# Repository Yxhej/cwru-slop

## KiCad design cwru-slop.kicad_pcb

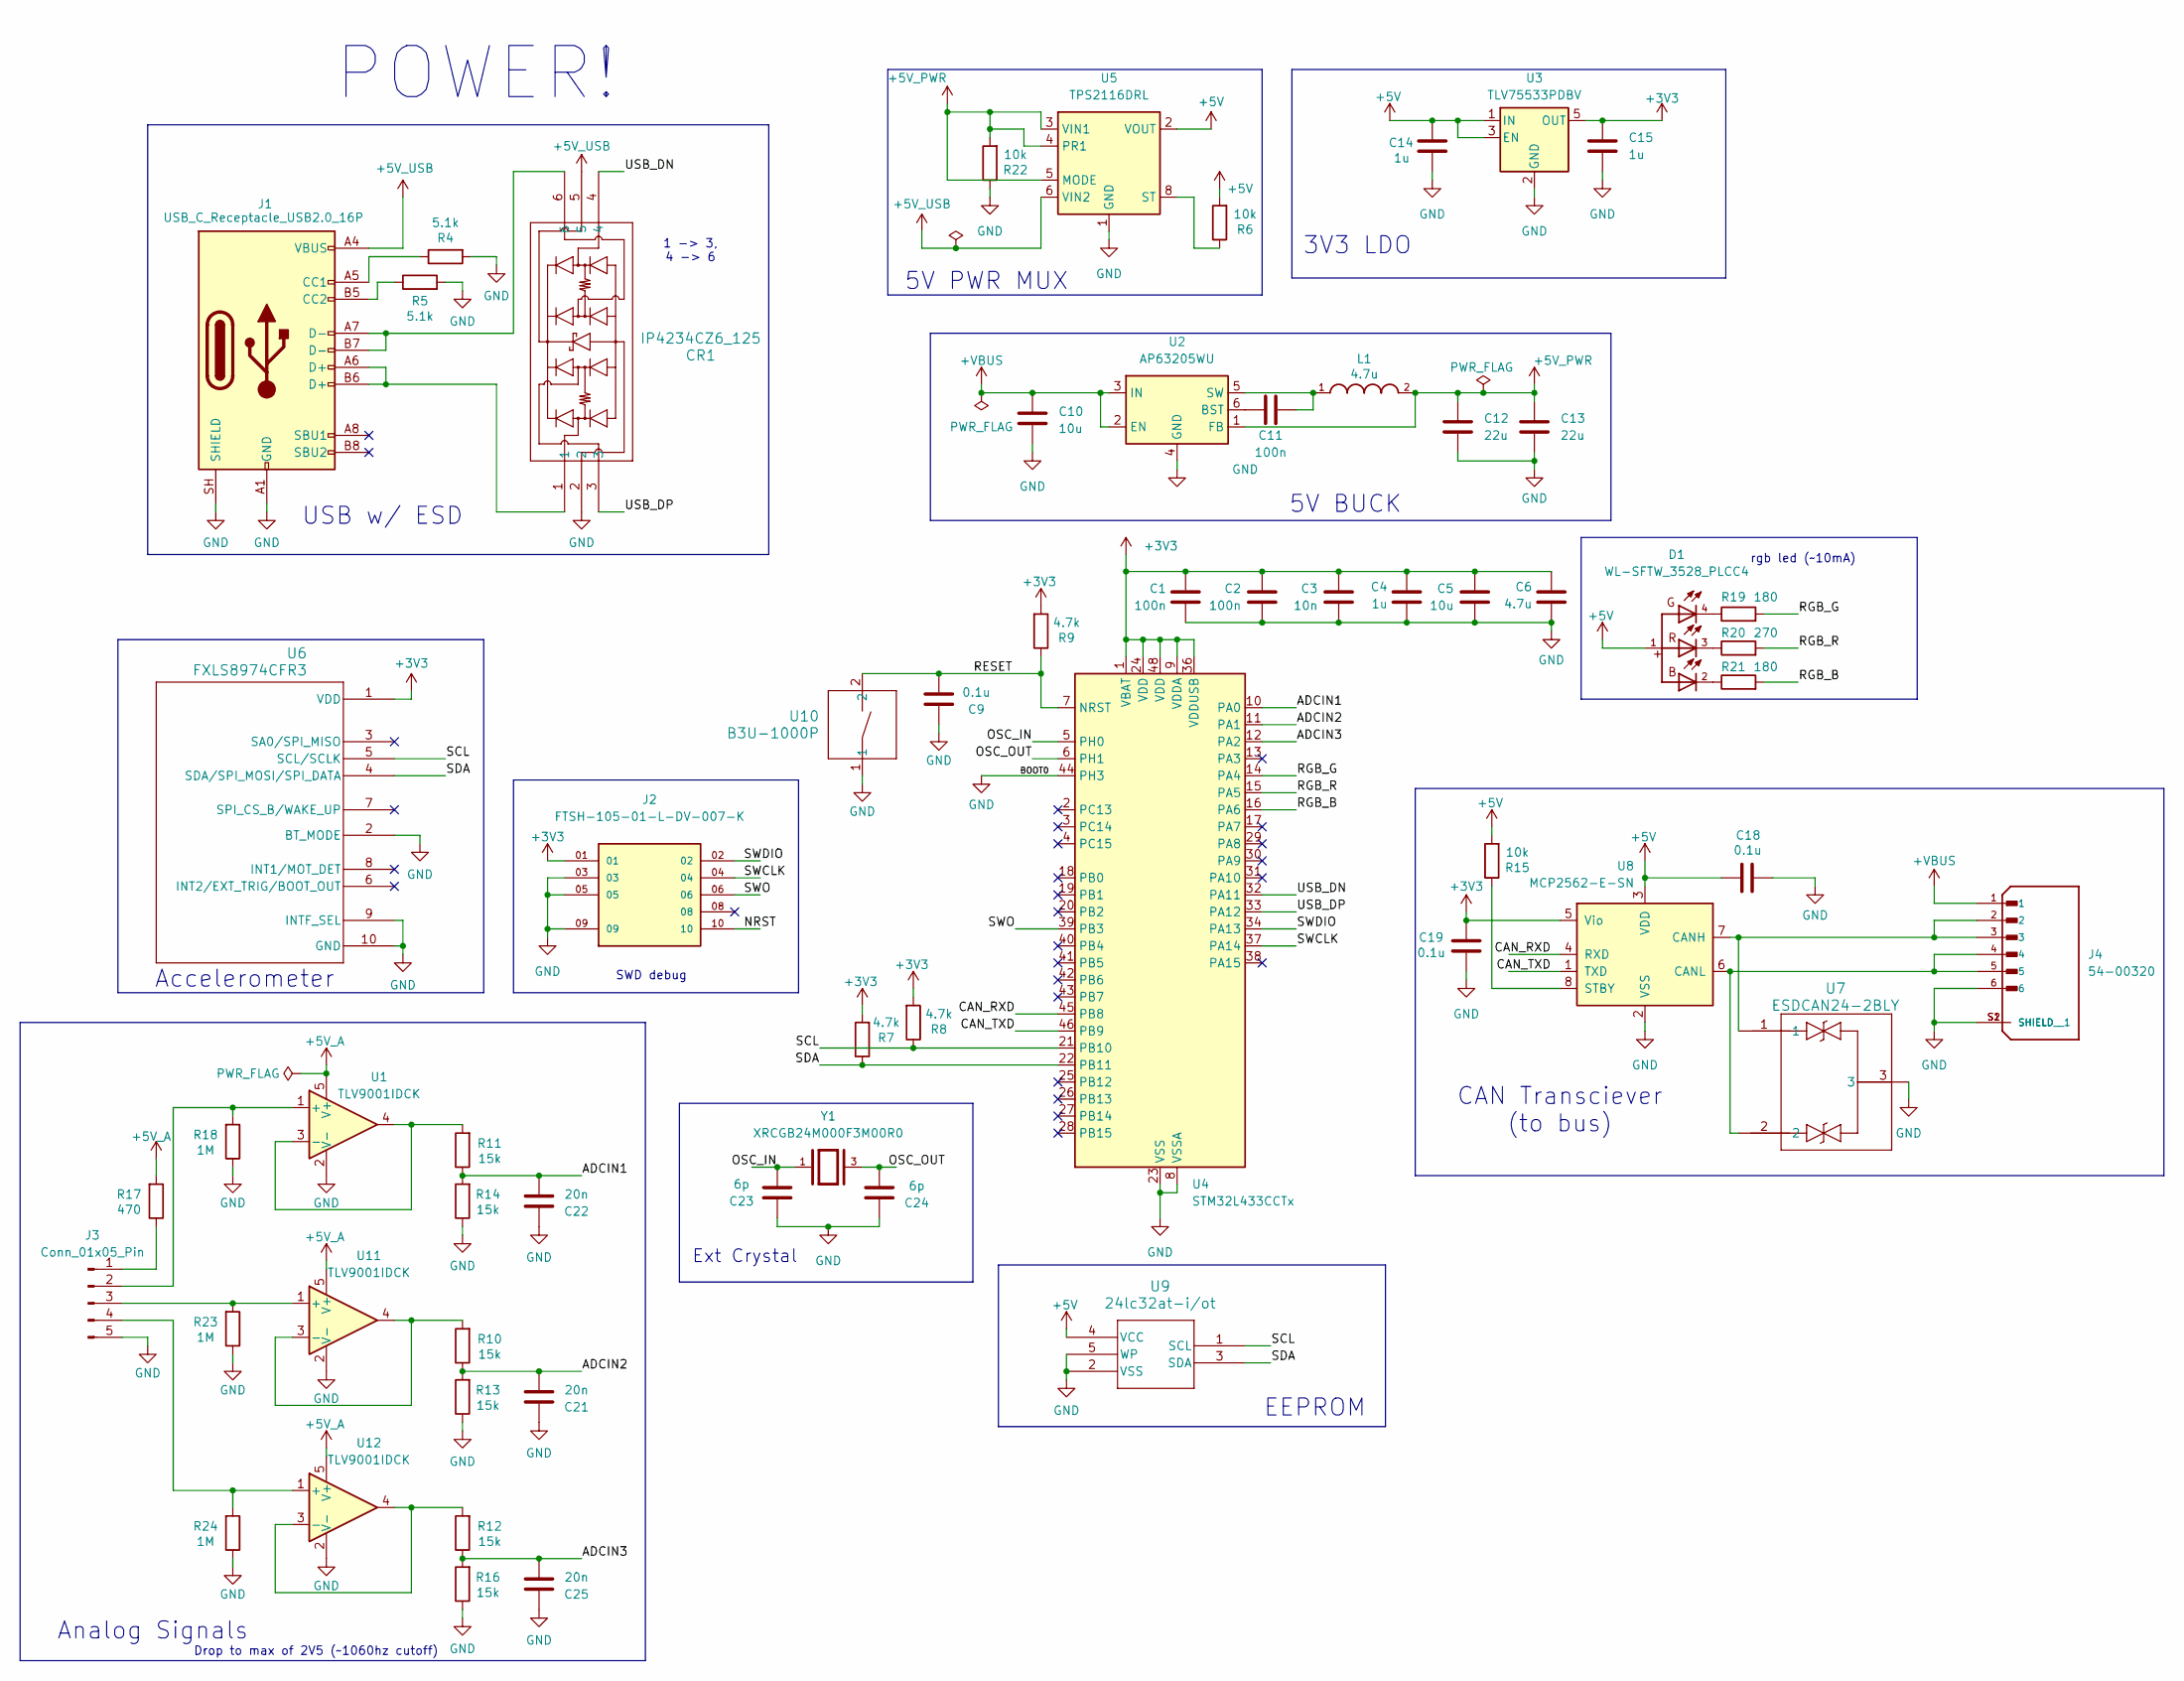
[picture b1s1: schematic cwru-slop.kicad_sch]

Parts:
C1, C2, C11: 100n; C_0603_1608Metric_Pad1.08x0.95mm_HandSolder
C3: 10n; C_0603_1608Metric_Pad1.08x0.95mm_HandSolder
C4, C14, C15: 1u; C_0603_1608Metric_Pad1.08x0.95mm_HandSolder
C5, C10: 10u; C_0603_1608Metric_Pad1.08x0.95mm_HandSolder
C6: 4.7u; C_0603_1608Metric_Pad1.08x0.95mm_HandSolder
C9, C18, C19: 0.1u; C_0603_1608Metric_Pad1.08x0.95mm_HandSolder
C12, C13: 22u; C_0603_1608Metric_Pad1.08x0.95mm_HandSolder
C21, C22, C25: 20n; C_0603_1608Metric_Pad1.08x0.95mm_HandSolder
C23, C24: 6p; C_0603_1608Metric_Pad1.08x0.95mm_HandSolder
CR1: IP4234CZ6_125; TSOP6_SOT457_NEX
D1: WL-SFTW_3528_PLCC4
J1: USB_C_Receptacle_USB2.0_16P; USB_C_Receptacle_GCT_USB4105-xx-A_16P_TopMnt_Horizontal
J2: FTSH-105-01-L-DV-007-K; SAMTEC_FTSH-105-01-L-DV-007-K; PARTREV H
J3: Conn_01x05_Pin; DIP-20_W7.62mm
J4: 54-00320; TENSILITY_54-00320; PARTREV A
L1: 4.7u; INDC2520X120N
R4, R5: 5.1k; R_0603_1608Metric_Pad0.98x0.95mm_HandSolder
R6, R15, R22: 10k; R_0603_1608Metric_Pad0.98x0.95mm_HandSolder
R7, R8, R9: 4.7k; R_0603_1608Metric_Pad0.98x0.95mm_HandSolder
R10, R11, R12, R13, R14, R16: 15k; R_0603_1608Metric_Pad0.98x0.95mm_HandSolder
R17: 470; R_0603_1608Metric_Pad0.98x0.95mm_HandSolder
R18, R23, R24: 1M; R_0603_1608Metric_Pad0.98x0.95mm_HandSolder
R19, R21: 180; R_0603_1608Metric_Pad0.98x0.95mm_HandSolder
R20: 270; R_0603_1608Metric_Pad0.98x0.95mm_HandSolder
U1, U11, U12: TLV9001IDCK; SOT-353_SC-70-5
U2: AP63205WU; TSOT-23-6
U3: TLV75533PDBV; SOT-23-5
U4: STM32L433CCTx; LQFP-48_7x7mm_P0.5mm
U5: TPS2116DRL; SOT-583-8
U6: FXLS8974CFR3; DFN10_2X2_STM
U7: ESDCAN24-2BLY; SOT_24-2BLY_STM
U8: MCP2562-E-SN; SOIC-8_3.9x4.9mm_P1.27mm
U9: 24lc32at-i/ot; SOT-24-5_MC_MCH
U10: B3U-1000P
Y1: XRCGB24M000F3M00R0; OSC_XRCGB24M000F3M00R0; PARTREV N/A

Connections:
+3V3: C1.1, C2.1, C3.1, C4.1, C5.1, C6.1, C15.1, C19.2, J2.01, R7.2, R8.2, R9.2, U3.5 (OUT), U4.1 (VBAT), U4.9 (VDDA), U4.24 (VDD), U4.36 (VDDUSB), U4.48 (VDD), U6.1 (VDD), U8.5 (Vio)
+5V: C14.1, C18.1, D1.1, R6.2, R15.2, U3.1 (IN), U3.3 (EN), U5.2 (VOUT), U5.7 (VOUT), U8.3 (VDD), U9.4 (VCC)
+5V_A: R17.2, U1.5 (V+), U11.5 (V+), U12.5 (V+)
+5V_PWR: C12.1, C13.2, L1.2, R22.2, U2.1 (FB), U5.3 (VIN1), U5.4 (PR1), U5.5 (MODE)
+5V_USB: CR1.5, J1.A4 (VBUS), J1.A9 (VBUS), J1.B4 (VBUS), J1.B9 (VBUS), U5.6 (VIN2)
+VBUS: C10.1, J4.1, U2.2 (EN), U2.3 (IN)
/ADCIN1: C22.2, R11.1, R14.2, U4.10 (PA0)
/ADCIN2: C21.2, R10.1, R13.2, U4.11 (PA1)
/ADCIN3: C25.2, R12.1, R16.2, U4.12 (PA2)
/CAN_RXD: U4.45 (PB8), U8.4 (RXD)
/CAN_TXD: U4.46 (PB9), U8.1 (TXD)
/NRST: J2.10
/OSC_IN: C23.2, U4.5 (PH0), Y1.1
/OSC_OUT: C24.2, U4.6 (PH1), Y1.3
/RESET: C9.2, R9.1, U4.7 (NRST), U10.2
/RGB_B: R21.2, U4.16 (PA6)
/RGB_G: R19.2, U4.14 (PA4)
/RGB_R: R20.2, U4.15 (PA5)
/SCL: R8.1, U4.21 (PB10), U6.5 (SCL/SCLK), U9.1 (SCL)
/SDA: R7.1, U4.22 (PB11), U6.4 (SDA/SPI_MOSI/SPI_DATA), U9.3 (SDA)
/SWCLK: J2.04, U4.37 (PA14)
/SWDIO: J2.02, U4.34 (PA13)
/SWO: J2.06, U4.39 (PB3)
/USB_DN: CR1.4, U4.32 (PA11)
/USB_DP: CR1.3, U4.33 (PA12)
GND: C1.2, C2.2, C3.2, C4.2, C5.2, C6.2, C9.1, C10.2, C12.2, C13.1, C14.2, C15.2, C18.2, C19.1, C21.1, C22.1, C23.1, C24.1, C25.1, CR1.2, J1.A1 (GND), J1.A12 (GND), J1.B1 (GND), J1.B12 (GND), J1.SH (SHIELD), J2.03, J2.05, J2.09, J3.5, J4.6, J4.S1 (SHIELD), J4.S2 (SHIELD__1), R4.2, R5.2, R13.1, R14.1, R16.1, R18.1, R22.1, R23.1, R24.1, U1.2 (V-), U2.4 (GND), U3.2 (GND), U4.8 (VSSA), U4.23 (VSS), U4.35 (VSS), U4.44 (PH3), U4.47 (VSS), U5.1 (GND), U6.2 (BT_MODE), U6.9 (INTF_SEL), U6.10 (GND), U7.3, U8.2 (VSS), U9.2 (VSS), U9.5 (WP), U10.1, U11.2 (V-), U12.2 (V-)
unnamed: CR1.1, J1.A6 (D+), J1.B6 (D+)
unnamed: CR1.6, J1.A7 (D-), J1.B7 (D-)
unnamed: D1.2, R21.1
unnamed: D1.3, R20.1
unnamed: D1.4, R19.1
unnamed: J1.A5 (CC1), R4.1
unnamed: J1.B5 (CC2), R5.1
unnamed: J3.1, R17.1
unnamed: J3.2, R18.2, U1.1 (+)
unnamed: J3.3, R23.2, U11.1 (+)
unnamed: J3.4, R24.2, U12.1 (+)
unnamed: R11.2, U1.3 (-), U1.4
unnamed: C11.1, U2.6 (BST)
unnamed: C11.2, L1.1, U2.5 (SW)
unnamed: R6.1, U5.8 (ST)
unnamed: J4.2, J4.3, U7.1, U8.7 (CANH)
unnamed: J4.4, J4.5, U7.2, U8.6 (CANL)
unnamed: R15.1, U8.8 (STBY)
unnamed: R10.2, U11.3 (-), U11.4
unnamed: R12.2, U12.3 (-), U12.4

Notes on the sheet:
Ext Crystal
3V3 LDO
CAN Transciever (to bus)
5V BUCK
Drop to max of 2V5 (~1060hz cutoff)
Analog Signals
rgb led (~10mA)
5V PWR MUX
POWER!
USB w/ ESD
SWD debug
1 -> 3, 4 -> 6
EEPROM
Accelerometer

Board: 2 copper layers, 61 parts (0 on the bottom side), 45 nets, no tracks yet.

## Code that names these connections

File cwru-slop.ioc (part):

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Mcu.Name=STM32L433C(B-C)Tx
Mcu.Package=LQFP48
Mcu.UserName=STM32L433CCTx
PA0.Signal=ADCx_IN5
PA1.Signal=ADCx_IN6
PA11.Mode=Device
PA11.Signal=USB_DM
PA12.Mode=Device
PA12.Signal=USB_DP
PA13\ (JTMS-SWDIO).Signal=SYS_JTMS-SWDIO
PA14\ (JTCK-SWCLK).Signal=SYS_JTCK-SWCLK
PA2.Signal=ADCx_IN7
PA4.Signal=GPIO_Output
PA5.Signal=GPIO_Output
PA6.Signal=GPIO_Output
PB10.Mode=I2C
PB10.Signal=I2C2_SCL
PB11.Mode=I2C
PB11.Signal=I2C2_SDA
PB3\ (JTDO-TRACESWO).Signal=SYS_JTDO-SWO
PB8.Mode=CAN_Activate
PB8.Signal=CAN1_RX
PB9.Mode=CAN_Activate
PB9.Signal=CAN1_TX
PH0-OSC_IN\ (PH0).Mode=HSE-External-Oscillator
PH0-OSC_IN\ (PH0).Signal=RCC_OSC_IN
PH1-OSC_OUT\ (PH1).Mode=HSE-External-Oscillator
PH1-OSC_OUT\ (PH1).Signal=RCC_OSC_OUT
RCC.HSE_VALUE=8000000
RCC.SYSCLKFreq_VALUE=80000000
RCC.SYSCLKSource=RCC_SYSCLKSOURCE_PLLCLK
board=custom
